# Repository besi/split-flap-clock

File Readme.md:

Split Flap clock or calendar utilising four 28BYJ-48 stepper motors.

## Bill of materials

What is needed for one digit.

| Count | Item                 | Description                       |
|-------|----------------------|-----------------------------------|
| 1     | PCB v2.0             |                                   |
| 1     | Supporting Plate     | Same shape and holes like the PCB |
| 1     | Spacer 2mm           | Spacer for cogwheels              |
| 1     | Hall sensor AH1815-W7| For the unpopulated PCBs only     |
| 1     | 10k Resistor 0306    | For the unpopulated PCBS          |
| 1     | Spool                | 3-D Print with M3 heat insert     |
| 1     | Spool lid            | 3-D Print                         |
| 1     | Cog Stepper          | 3-D Print / Laser cut             |
| 1     | Cog M3               | 3-D Print / Laser cut             |
| 1     | Cog M3 Nut           | 3-D Print / Laser cut             |
| 1     | Magnet 2x1mm         | For spool                         |
| 1     | Motor 28BYJ-48       | 5V Version                        |
| 1     | Motor gasket         | Laser cut                         |
| 12    | Flaps                | Laser cut Flaps                   |
| 1     | 3 Pos JST 2mm Socket | Hall sensor Connection            |
| 1     | 3 Pos JST 2mm Cable  | Hall sensor Connection            |
| 4     | M3 Nuts              | 2 Cogs, 2 Motor                   |
| 5     | M3x8mm Bolt          | 2 Cogs,2 Motor, Spindle,          |
| 3     | M3x5mm Bolt          | 3 Spindle                         |
| 4     | M3 Standoffs 50mm    | Male-Female 6mm thread            |
| 4     | M2.5 Screws          | For Standoffs                     |
| 1     | Washer 5mm 1mm thick | For Driver cogwheel               |
| 2     | Washer 3mm 1mm thick | For cogwheels                     |
| 1     | Zip tie for motor    |                                   |

## Pinout

Motors: 

| Pins        | 1  | 2  | 3  | 4  | Hall  |
|-------------|----|----|----|----|-------|
| **Motor A** | 10 | 9  | 3  | 8  | 18 (7)|
| **Motor B** | 13 | 14 | 21 | 11 | 12    |
| **Motor C** | 40 | 39 | 38 | 6  | 47    |
| **Motor D** | 1  | 2  | 42 | 41 | 48    |

Other GPIOs

| Function       | Pin |
|----------------|-----|
| DCF-77         | 4   |
| SDA / Switch B | 16  |
| SCL / Switch A | 17  |
| Mode           | 0   |
| Neopixel       | 15  |
| Temperature    | 5   |

## Assembly

One assembled PCB which functions as the main board can drive four split flap digits including itself as well as three additional passive digits. Looking from the front of the clock / calendar the unit with the populated PCB is to the very left with the barrel jack protruding outward to the left side.

- On the three unpopulated PCBs the Hall sensors circuitry above the spool axis has to be provided. For this R7 can be shortened using a solder bridge, the Hall sensor (AH1815-W7) as well as the R1 resistor (10k 0603) need to be mounted. C1 (100nF 0603) can be omitted:  

- Using M3x5 screws mount all four motors directly to the corresponding PCB using the spacer where it says "28BYJ-48". The nuts go to the other side of the PCB where the spacer has two cutouts for both nuts.

- On the main board connect the motor to the "Motor A" connector. The cable can be looped and secured using a zip tie threaded through the two holes next to the motor.

- On the main board solder the three switches and the RGB LED to the backside of the PCB.

- Solder the DCF77 connector to the pcb and temporarily tape the ferrite antenna to the PCB to protect the thin copper wires from the coil around the antenna.

- Add cog wheels with the M3x8 screws on two different sides
- Add the spacer
- Add the cover
- Connect all hall sensors
- Prepare the spool 
- Add standoffs female-female or standoffs male-female respectively

- The driving cog wheel is assembled as follows:

        M3x16 + 5 washers + m3-nut-cog + 3 washers

## The PCB

[PCBWay][pcbway] kindly offered to sponsor the manufacturing and assembly of the second iteration of this pcb.

[][pcbway]

In this project the PCBs are used in both the electrical as well as the mechanical realm. The motors and cog wheels are directly mounted onto the pcb and for one clock or calendar four pcbs are stacked together.

The PCBs turned out flawlessly and the ordering process was smooth and efficient.

[pcbway]: https://pcbway.com/g/2jc702

### PCB V2.0

### PCB V1.0

## Flashing the PCB

    cd ~/Downloads
    IMAGE=ESP32_GENERIC_S3-20251209-v1.27.0.bin
    wget https://micropython.org/resources/firmware/$IMAGE -nc
    PORT=/dev/cu.usbmodem14401
    esptool.py --port $PORT erase_flash
    esptool.py --port $PORT --baud 460800 write_flash --flash_size=detect 0 $IMAGE --flash_mode=dout

## Credits

### 3d models
- Credits for the [ESP32 Devkit 3d model](https://grabcad.com/library/esp32-devkitc-v4-1) by [Andrei Golyakov](https://grabcad.com/andrei.golyakov-1)
- Credits for the [SK6814mini 3d model](https://grabcad.com/library/sk6812-mini-sk6814-smd3535-1) by [Laur V](https://grabcad.com/laur.v-1)

### Markdown tables

The Markdown tables were generated using the fabulous tool called [tableconvert](https://tableconvert.com/markdown-generator).

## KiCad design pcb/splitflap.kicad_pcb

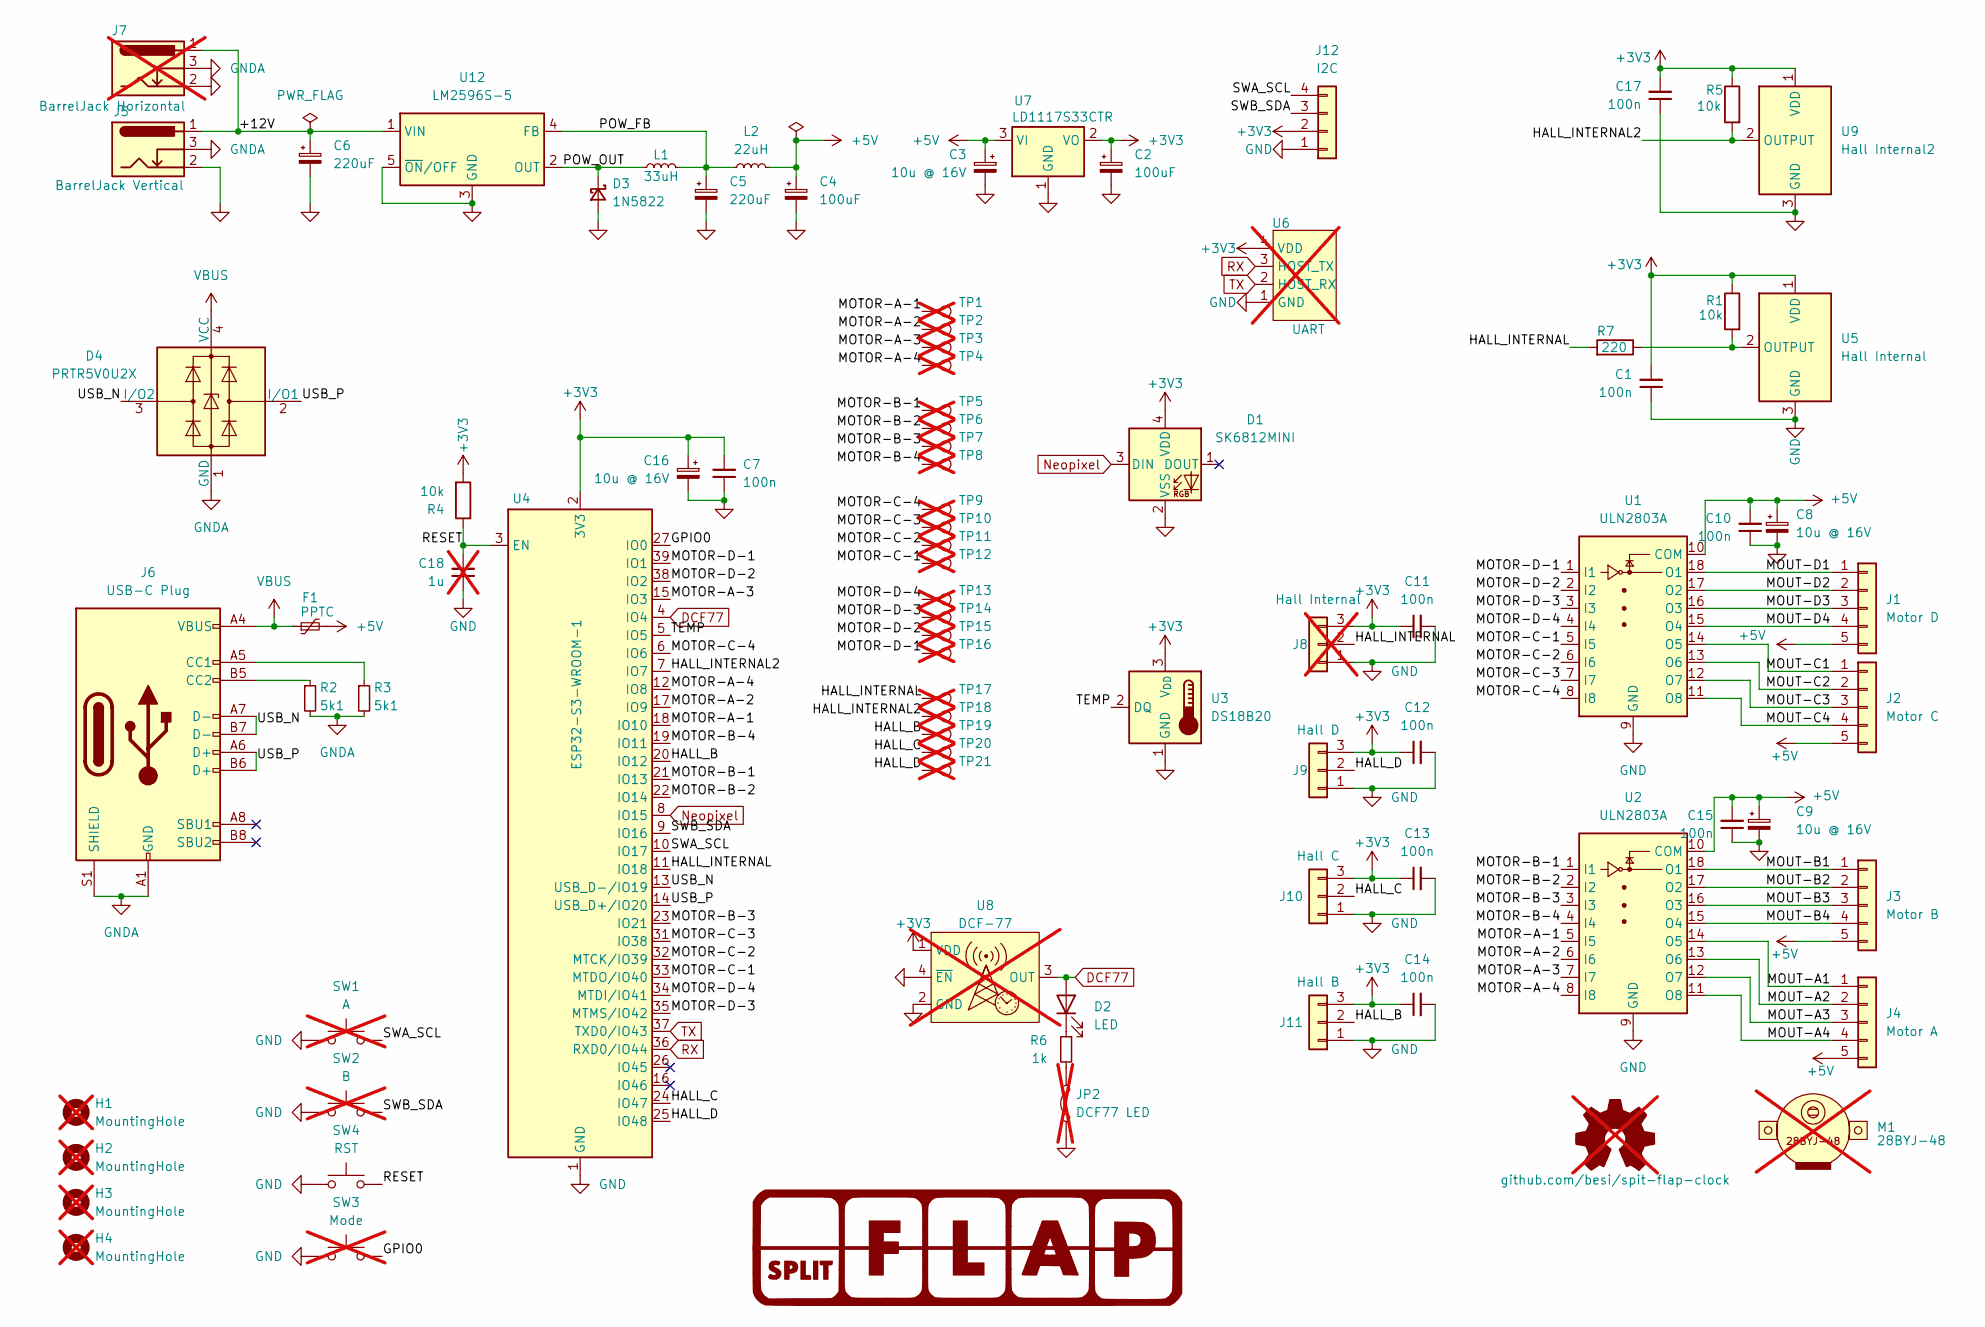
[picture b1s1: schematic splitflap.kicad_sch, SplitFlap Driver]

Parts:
C1, C7, C10, C11, C12, C13, C14, C15, C17: 100n; C_0603_1608Metric; MPN CL10E104KC8VPNC
C2, C4: 100uF; CP_Elec_5x5.3; MPN APXG160ARA101ME61G
C3, C8, C9, C16: 10u @ 16V; CP_Elec_4x5.7; MPN 865080340001
C5, C6: 220uF; CP_Elec_8x11.9; MPN A768KS227M1VLAE024
C18: 1u; C_0805_2012Metric_Pad1.18x1.45mm_HandSolder; MPN CL21B105KOFNNNG; not fitted
D1: SK6812MINI; LED_SK6812MINI_PLCC4_3.5x3.5mm_P1.75mm; MPN 1528-1541-ND
D2: LED; LED_0603_1608Metric_Pad1.05x0.95mm_HandSolder; MPN 150060RS75000
D3: 1N5822; D_DO-201_P15.24mm_Horizontal; MPN 1N5822
D4: PRTR5V0U2X; SOT-143; MPN PRTR5V0U2X,215
F1: PPTC; Fuse_1206_3216Metric; MPN MF-NSMF110/16X-2
H1, H2, H3, H4: MountingHole; MountingHole_3.2mm_M3; MPN X; LCSC DNP; not fitted
J1: Motor D; JST_XH_B5B-XH-A_1x05_P2.50mm_Vertical; MPN B5B-XH-A
J2: Motor C; JST_XH_B5B-XH-A_1x05_P2.50mm_Vertical; MPN B5B-XH-A
J3: Motor B; JST_XH_B5B-XH-A_1x05_P2.50mm_Vertical; MPN B5B-XH-A
J4: Motor A; JST_XH_B5B-XH-A_1x05_P2.50mm_Vertical; MPN B5B-XH-A
J5: BarrelJack Vertical; pj-060a; MPN CP-060A-ND
J6: USB-C Plug; USB_C_Receptacle_GCT_USB4105-xx-A_16P_TopMnt_Horizontal; MPN USB4105-GF-A
J7: BarrelJack Horizontal; BarrelJack_GCT_DCJ200-10-A_Horizontal; MPN 2073-DCJ200-10-A-K1-K-ND; not fitted
J8: Hall Internal; JST_PH_B3B-PH-K_1x03_P2.00mm_Vertical; MPN B3B-PH-K-S; not fitted
J9: Hall D; JST_PH_B3B-PH-K_1x03_P2.00mm_Vertical; MPN B3B-PH-K-S
J10: Hall C; JST_PH_B3B-PH-K_1x03_P2.00mm_Vertical; MPN B3B-PH-K-S
J11: Hall B; JST_PH_B3B-PH-K_1x03_P2.00mm_Vertical; MPN B3B-PH-K-S
J12: I2C; JST_SH_BM04B-SRSS-TB_1x04-1MP_P1.00mm_Vertical; MPN BM04B-SRSS-TB
JP2: DCF77 LED; SolderJumper-2_P1.3mm_Bridged_RoundedPad1.0x1.5mm; MPN X; not fitted
L1: 33uH; L_APV_ANR6028; MPN NR6028T330M
L2: 22uH; L_APV_ANR5045; MPN TYS5040220M-10
M1: 28BYJ-48; 28byj; MPN 28BYJ-48; not fitted
OSHW1: github.com/besi/spit-flap-clock; OSHW-Symbol_6.7x6mm_SilkScreen; MPN X; not fitted
R1, R5: 10k; R_0603_1608Metric; MPN CR0603-FX-1002ELF
R2, R3: 5k1; R_0603_1608Metric; MPN CR0603-FX-5101ELF
R4: 10k; R_0603_1608Metric_Pad0.98x0.95mm_HandSolder; MPN CR0603-FX-1002ELF
R6: 1k; R_0603_1608Metric; MPN CR0603-JW-102ELF
R7: 220; R_0603_1608Metric; MPN CR0603-JW-221ELF
SW1: A; SW_Push_1P1T_NO_Vertical_Wuerth_434133025816; MPN PTS815SJM250SMTRLFS; not fitted
SW2: B; SW_Push_1P1T_NO_Vertical_Wuerth_434133025816; MPN PTS815SJM250SMTRLFS; not fitted
SW3: Mode; SW_Push_1P1T_NO_Vertical_Wuerth_434133025816; MPN PTS815SJM250SMTRLFS; not fitted
SW4: RST; SW_Push_1P1T_NO_Vertical_Wuerth_434133025816; MPN PTS815SJM250SMTRLFS
TP1, TP2, TP3, TP4, TP5, TP6, TP7, TP8, TP9, TP10, TP11, TP12, TP13, TP14, TP15, TP16, TP17, TP18, TP19, TP20, TP21: TestPoint; TestPoint_Pad_D1.0mm; MPN X; not fitted
U1, U2: ULN2803A; SOP-18_7.495x11.515mm_P1.27mm; MPN 4518-ULN2803ATR-ND
U3: DS18B20; TO-92S; MPN 4518-DS18B20-ND
U4: ESP32-S3-WROOM-1; MPN ESP32-S3-WROOM-1-N4
U5: Hall Internal; SC-59_Handsoldering; MPN AH1815-W-7
U6: UART; PinHeader_1x04_P2.54mm_Vertical; MPN X; not fitted
U7: LD1117S33CTR; SOT-223-3_TabPin2; MPN LD1117S33CTR
U8: DCF-77; dcf77; MPN X; not fitted
U9: Hall Internal2; SC-59_Handsoldering; MPN AH1815-W-7
U12: LM2596S-5; TO-263-5_TabPin3; MPN 5399-LM2596S-5.0CT-ND

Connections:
+3V3: C1.2, C2.1, C7.2, C11.1, C12.1, C13.1, C14.1, C16.1, C17.2, D1.4 (VDD), J8.3, J9.3, J10.3, J11.3, J12.2, R1.1, R4.2, R5.1, U3.3 (V_{DD}), U4.2 (3V3), U5.1 (VDD), U6.4 (VDD), U7.2 (VO), U8.1 (VDD), U9.1 (VDD)
+5V: C3.1, C4.1, C8.1, C9.1, C10.2, C15.2, F1.2, J1.5, J2.5, J3.5, J4.5, L2.2, U1.10 (COM), U2.10 (COM), U7.3 (VI)
/+12V: C6.1, J5.1, J7.1, U12.1 (VIN)
/GPIO0: SW3.2, U4.27 (IO0)
/HALL_B: J11.2, TP19.1, U4.20 (IO12)
/HALL_C: J10.2, TP20.1, U4.24 (IO47)
/HALL_D: J9.2, TP21.1, U4.25 (IO48)
/HALL_INTERNAL: J8.2, R7.2, TP17.1, U4.11 (IO18)
/HALL_INTERNAL2: R5.2, TP18.1, U4.7 (IO7), U9.2 (OUTPUT)
/MOTOR-A-1: TP1.1, U2.5 (I5), U4.18 (IO10)
/MOTOR-A-2: TP2.1, U2.6 (I6), U4.17 (IO9)
/MOTOR-A-3: TP3.1, U2.7 (I7), U4.15 (IO3)
/MOTOR-A-4: TP4.1, U2.8 (I8), U4.12 (IO8)
/MOTOR-B-1: TP5.1, U2.1 (I1), U4.21 (IO13)
/MOTOR-B-2: TP6.1, U2.2 (I2), U4.22 (IO14)
/MOTOR-B-3: TP7.1, U2.3 (I3), U4.23 (IO21)
/MOTOR-B-4: TP8.1, U2.4 (I4), U4.19 (IO11)
/MOTOR-C-1: TP12.1, U1.5 (I5), U4.33 (MTDO/IO40)
/MOTOR-C-2: TP11.1, U1.6 (I6), U4.32 (MTCK/IO39)
/MOTOR-C-3: TP10.1, U1.7 (I7), U4.31 (IO38)
/MOTOR-C-4: TP9.1, U1.8 (I8), U4.6 (IO6)
/MOTOR-D-1: TP16.1, U1.1 (I1), U4.39 (IO1)
/MOTOR-D-2: TP15.1, U1.2 (I2), U4.38 (IO2)
/MOTOR-D-3: TP14.1, U1.3 (I3), U4.35 (MTMS/IO42)
/MOTOR-D-4: TP13.1, U1.4 (I4), U4.34 (MTDI/IO41)
/MOUT-A1: J4.1, U2.14 (O5)
/MOUT-A2: J4.2, U2.13 (O6)
/MOUT-A3: J4.3, U2.12 (O7)
/MOUT-A4: J4.4, U2.11 (O8)
/MOUT-B1: J3.1, U2.18 (O1)
/MOUT-B2: J3.2, U2.17 (O2)
/MOUT-B3: J3.3, U2.16 (O3)
/MOUT-B4: J3.4, U2.15 (O4)
/MOUT-C1: J2.1, U1.14 (O5)
/MOUT-C2: J2.2, U1.13 (O6)
/MOUT-C3: J2.3, U1.12 (O7)
/MOUT-C4: J2.4, U1.11 (O8)
/MOUT-D1: J1.1, U1.18 (O1)
/MOUT-D2: J1.2, U1.17 (O2)
/MOUT-D3: J1.3, U1.16 (O3)
/MOUT-D4: J1.4, U1.15 (O4)
/POW_FB: C5.1, L1.2, L2.1, U12.4 (FB)
/POW_OUT: D3.1 (K), L1.1, U12.2 (OUT)
/RESET: C18.2, R4.1, SW4.2, U4.3 (EN)
/SWA_SCL: J12.4, SW1.2, U4.10 (IO17)
/SWB_SDA: J12.3, SW2.2, U4.9 (IO16)
/TEMP: U3.2 (DQ), U4.5 (IO5)
/USB_N: D4.3 (I/O2), J6.A7 (D-), J6.B7 (D-), U4.13 (USB_D-/IO19)
/USB_P: D4.2 (I/O1), J6.A6 (D+), J6.B6 (D+), U4.14 (USB_D+/IO20)
DCF77: D2.2 (A), U4.4 (IO4), U8.3 (OUT)
GND: C1.1, C2.2, C3.2, C4.2, C5.2, C6.2, C7.1, C8.2, C9.2, C10.1, C11.2, C12.2, C13.2, C14.2, C15.1, C16.2, C17.1, C18.1, D1.2 (VSS), D3.2 (A), J5.2, J7.2, J8.1, J9.1, J10.1, J11.1, J12.1, JP2.1 (A), SW1.1, SW2.1, SW3.1, SW4.1, U1.9 (GND), U2.9 (GND), U3.1 (GND), U4.1 (GND), U4.40 (GND), U4.41 (GND), U5.3 (GND), U6.1 (GND), U7.1 (GND), U8.2 (GND), U8.4 (~EN), U9.3 (GND), U12.3 (GND), U12.5 (~ON/OFF)
GNDA: D4.1 (GND), J5.3, J6.A1 (GND), J6.A12 (GND), J6.B1 (GND), J6.B12 (GND), J6.S1 (SHIELD), J7.3, R2.2, R3.2
Neopixel: D1.3 (DIN), U4.8 (IO15)
unnamed: D2.1 (K), R6.1
unnamed: J6.A5 (CC1), R3.1
unnamed: J6.B5 (CC2), R2.1
unnamed: JP2.2 (B), R6.2
unnamed: R1.2, R7.1, U5.2 (OUTPUT)
RX: U4.36 (RXD0/IO44), U6.3 (HOST_TX)
TX: U4.37 (TXD0/IO43), U6.2 (HOST_RX)
VBUS: D4.4 (VCC), F1.1, J6.A4 (VBUS), J6.A9 (VBUS), J6.B4 (VBUS), J6.B9 (VBUS)

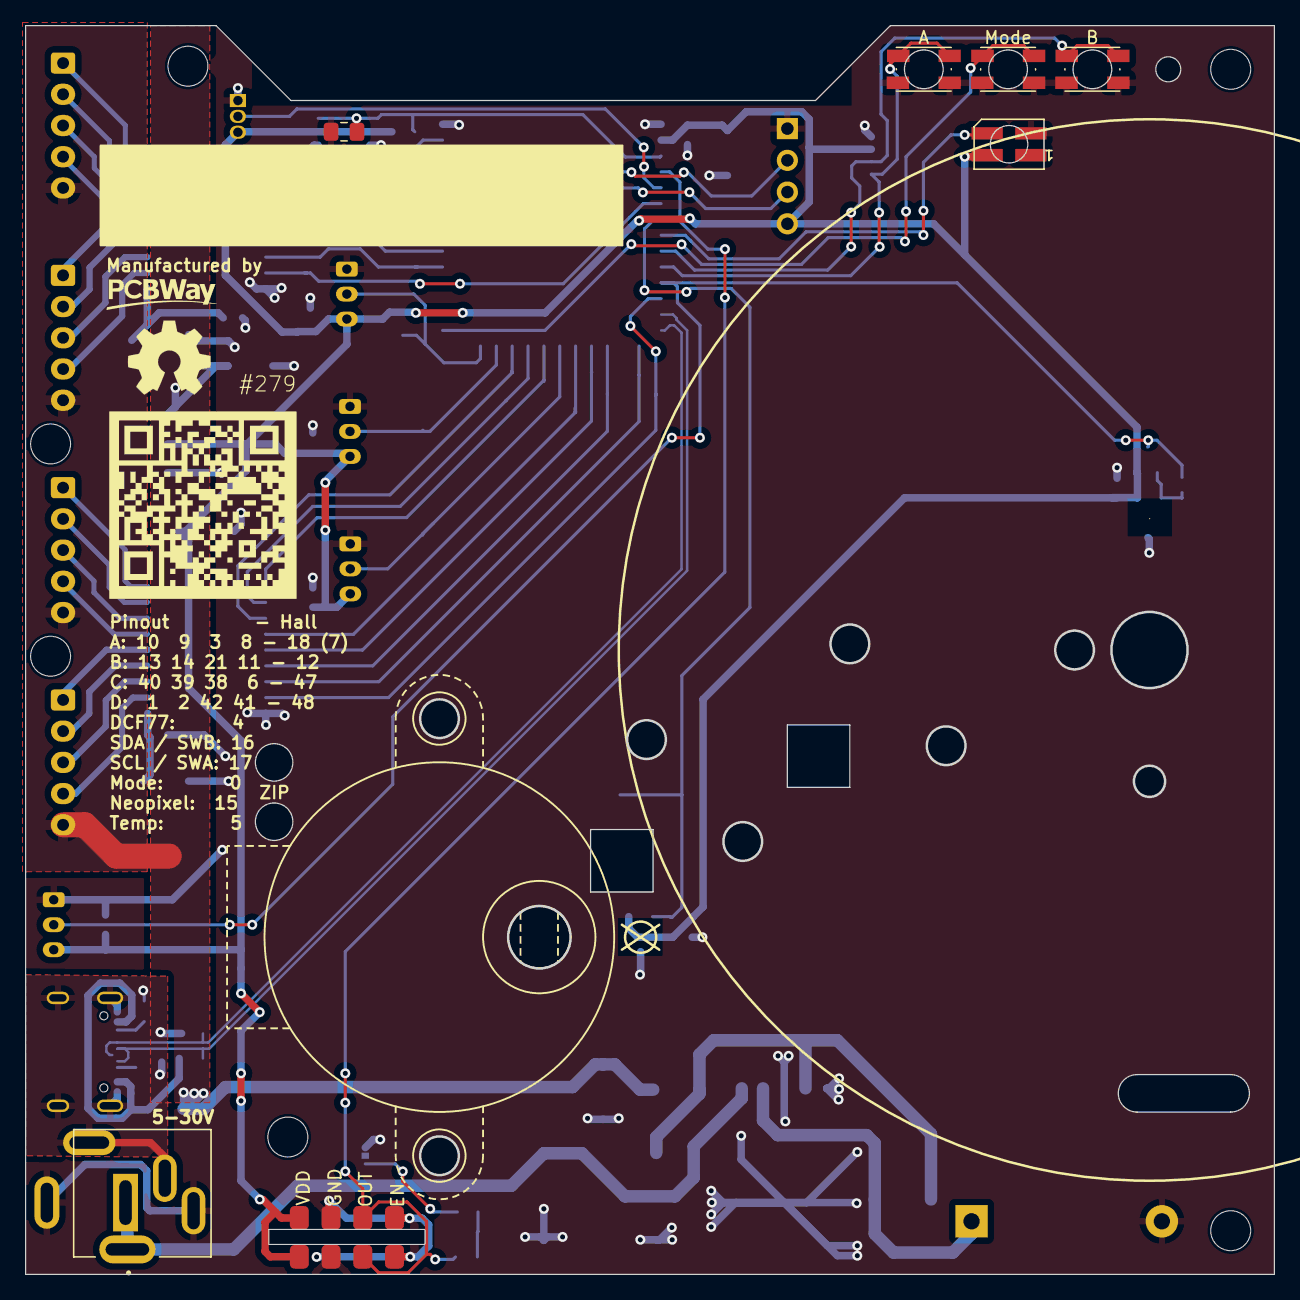
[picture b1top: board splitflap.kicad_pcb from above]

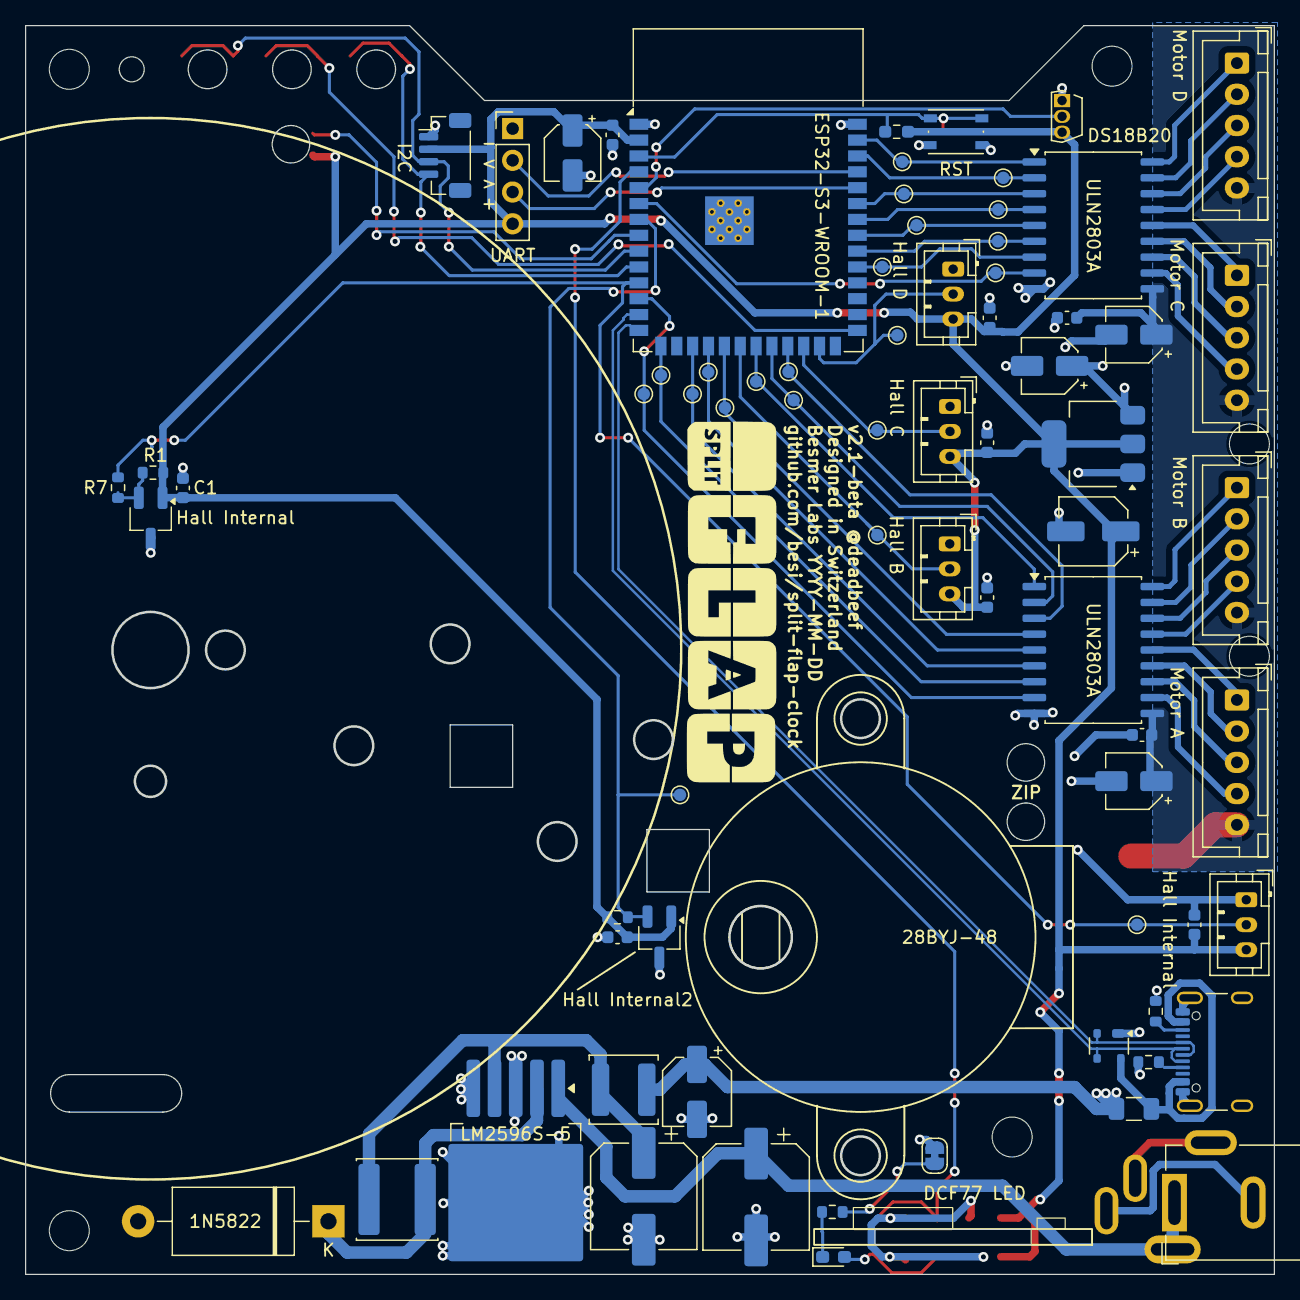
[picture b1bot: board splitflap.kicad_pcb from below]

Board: 2 copper layers, 99.9 x 99.9 mm, 88 parts (81 on the bottom side), 61 nets.

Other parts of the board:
H5, H6: MountingHole; MountingHole_3.2mm_M3

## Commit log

2025-01-18 Add readme
2025-01-19 Add dxf for the case - v1
2025-01-19 Don't add the makercase screenshot
2025-01-19 Added 2mm housing
2025-01-19 Fixed wrong material thickness
2025-01-19 Updated screenshot
2025-01-20 Add software
2025-01-20 Add flaps of v2
2025-01-21 Add 3d files
2025-01-21 new case for v2
2025-01-21 Add filet to front
2025-01-21 Add stl
2025-01-21 update screenshot
2025-01-25 Add intial pcb for the split flap calender multi-motor setup
2025-01-26 Silkscreen and documentation
2025-01-26 Add Logo
2025-01-26 Silkscreen and hall sensor breakout cleanup
2025-01-26 Panelise the Hall sensor breakout
2025-01-26 Add a barrel jack and include all hall breakouts in the schematic
2025-01-26 Add measurements
2025-01-26 Cleanup schematic
2025-01-26 Add four buttons A, B, GPIO0 and RST
2025-01-26 Set the board origin for step export and prepare for next release
2025-01-28 Add esp 32 wroom step file
2025-01-29 Make sure mouse bites aren't deleted upon import
2025-02-03 Add 12V-enabled power supply
2025-02-04 Add missing footprint
2025-02-04 Add qwiic adapter
2025-02-04 Run DRC and ERC
2025-02-04 .gitignore
2025-02-04 Prepare for production
2025-02-05 Version 1.1-beta
2025-02-05 Upcoming release
2025-02-08 Add gears
2025-02-09 Allow skipping the WIFI in boot.py
2025-02-09 Add 18n gears
2025-02-17 Make SOIC16 package of ULN2003 more wide and label both inductors with silkscreen
2025-02-17 Add package to schematic for SOIC16 ULN2003
2025-02-18 Hardware test
    See #1
2025-02-18 Test for buttons
    see #1
2025-02-22 Add 3d model of the pcb
2025-02-28 Update to stepper code
2025-02-28 Alternate aparently more responsive motor mapping
2025-02-28 Allow testing all the steppers
2025-02-28 Add micropython board identifier
2025-02-28 Add upcoming todo
2025-03-01 Add todos
2025-03-01 HW Test script so the programming in main.py can start
2025-03-01 Add digit class which allows to control one digit
2025-03-01 fine tune the calibration process for the digits
2025-03-01 Allow to jump to a given value
2025-03-02 Update schematic to aid troubleshooting
2025-03-04 Update digit to show all four digits
2025-03-04 Enable Wifi
2025-03-04 show the time at startup
2025-03-04 cleanup code
2025-03-04 Fix wrong labels in PCB
2025-03-04 Fix an error with a reference to the wrong hall sensor
2025-03-04 Adjust for angle
2025-03-04 Rework 1
    Per EE.SO answer https://electronics.stackexchange.com/a/740530/10810
2025-03-04 Rework 3
    Now the signal flow is the recommended way: inputs far away from power outputs. The Hall sensor connectors have been moved to the front of the PCB.
2025-03-04 Rework 2
    To be conservative, the traces driving the ULN2003s have been separated out, to prevent capacitive coupling between them. It's "cargo cult engineering", but since we can do it without trouble, how ab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
2025-03-04 Rework 4
    The trace from the 12V input capacitor to the switcher ran on the bottom layer, making for a rather deep cut in the ground plane. This trace has been partially moved to the top layer, avoiding the cu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
2025-03-04 Rework 5
    The schematic was separated into two sheets, and made easier to follow.
    The Neopixels were connected in parallel. They should be in series.
    The I2C mezzanine board was centered relative to the ESP module.
2025-03-05 Rework 6
    Added power flags to external power inputs. Fixed Motor connector pins from Unspecified to Passive, per KiCad fashion. Made the ERC pass without exclusions.
    Added power decoupling to Hall sensor connectors and to the Neopixels.
    Moved the IN test point for better probing accessibility. Test points use teardrop connections for integrity in face of probing.
    Added a ground clip area for scope probes etc.
    Added a 3D model of the pushbuttons.
    Rework 6
2025-03-05 Ignore library backup files (.bak).
2025-03-05 Add an image of the working prototype
2025-03-08 Draft of v2 board to be imported in Fusion360
2025-03-11 SW: Add the corrections as a seperate variable
2025-03-11 Allow to skip the offset move after the calibration in order to save revolutions at startup
2025-03-11 Cleanup calibration and main.py
2025-03-14 V2 WIP
2025-03-14 Add step files of the libraries
2025-03-14 Make the zip tie holes vertical
2025-03-14 Make cable winding holes bigger
2025-03-15 Small changes
    - Rename 4341x30258x6_rev1.stp to 434133025816.step
2025-03-15 Cleanup libraries
2025-03-15 Add extra test point for IO7 and an additional hall sensor for Hall A
2025-03-16 Make GNDA a power line
2025-03-16 Cleanup tracks
2025-03-17 Silkscreen improvements
2025-03-18 Show the current day after calibration of each digit
2025-03-18 Added 3d model of the SK6812 mini
2025-03-20 Add optional LED for DCF receiver
2025-03-20 Add two Hall sensors to the current board so that the amount of backlash can be registered
2025-03-20 Remapping the motors ABCD to match the connectors on the board
2025-03-20 Add capacitors for hall sensors power pins
2025-03-20 DNP components and bigger pads for hand solder items
2025-03-20 Run DRC
2025-03-21 Add new pcb design to the Readme
2025-03-21 Add flap stop slot
2025-03-21 Add a PPTC fuse to the USB connection
2025-03-21 Add test points for motor input signals and hall sensors
2025-03-21 Use 0603 for resistors and capacitors
2025-03-21 Update DNP field
2025-03-22 Add ESD protection for the USB-C socket
2025-03-22 Change package of the temperature sensor
2025-03-23 Cleanup MPNs
2025-03-23 Finalise MPNs
2025-03-23 Finalise the part’s MPN
2025-03-23 Unambiguous MPN for the TVS diode array
2025-03-23 Move silkscreen to Fab layers
2025-03-24 Populate the barrel jack on the back (if possible) and add a keep out zone for both hall sensors just in case
2025-03-24 Add logo to the PCB
2025-03-24 Silkscreen: Logo / Date / Commit Placeholder / Labels / PCB Way logo
2025-03-24 Add Pinout
2025-03-25 Fix HALL_INTERNAL label
    The layout is not affected
2025-03-25 Move images to `assets` folder
2025-03-25 Add version 1 and 2 to the Readme
2025-03-25 Add PCBWay sponsoring note to Readme
2025-03-25 Cleanup schematics
2025-03-25 Move vias out of the pads
2025-03-25 Correlate footprints according to the feedback from the Fab-house
2025-03-25 Add step model for the NR6028T330M inductor
2025-03-25 Prepare for fab-house
2025-03-25 Update credits in Readme
2025-03-26 Add Pinout to the Reamde
2025-03-26 Prepare for next release
2025-03-26 Line breaks in readme
2025-04-10 Add 18-theethed gears
2025-04-10 Add v1.2 stl files
2025-04-10 Add stl files based on fusion v19
2025-04-10 Cleanup stl files
2025-04-10 Add pcb for making support plates
2025-04-10 Add flaps SVG
2025-04-10 Add plot directory
2025-04-10 Settings for plotting
2025-05-04 Add credits for the markdown tables
2025-05-04 Add bill of materials for the V2.0 PCB
2025-05-07 Add spacer
2025-05-07 Add cog wheels as stl epxports
2025-05-07 Add washers to BOM
2025-05-07 Update v2 3d printing parts
2025-05-07 Add spacers
2025-05-07 Make some room inside the spacer
2025-05-07 Add zip ties to BOM
2025-05-08 m3 holes are now 3.2 mm and the cogs are 2.8mm thick
2025-05-08 Reference heat insert for 3d printed spool
2025-05-08 Update Backplate spacer
2025-05-08 Update spool and spool lid
2025-05-09 Add preliminary Flap design
2025-05-10 Describe how the spool cog is assembled
2025-05-10 Describe which hall sensor is used
2025-05-10 Configure first stepper for v2 pcb
2025-05-10 Fix utime vs. time lib
2025-05-10 make the cogs 2.5 mm and improve the magnet holder to better fit the 2mm magnets
2025-05-10 Add lower part to the flap
2025-05-16 Assembly notes
2025-05-16 Update the Readme with details on how to flash the device
2025-05-16 Fix error with utime
2025-05-16 Enable all digits
2025-05-16 Configure for v2.0 pcb
2025-05-18 Change TX Power to 5 rather than 20
    fixes #10
2025-05-18 Test the neopixel
    See #7
2025-05-18 Show the entire date upon update
2025-05-18 Show blank number for single digits
2025-05-18 Test Neopixel
    See #7
2025-05-18 Test buttons and I2C
    See #7
2025-05-18 The number digits should both start at 0
2025-05-24 Update digit position
2025-05-24 Formatting
2025-05-24 Only activate the wifi interface if internet is enabled
2025-05-25 Add flap toucher dxf
2025-05-25 Add dependencies
2025-05-26 Add flap pair
2025-05-26 Ignore lightburn files
2025-05-27 Add photo of the finished calendar
2025-05-27 Typo
2025-05-27 Flap changes: 7mm Tab / Extra wiggle 0.5 each side / round of Flap corners
2025-06-01 Show an empty flap for leading zeros of the date
2025-06-08 Make the 11th flap the blank so that a new number is more quickly shown
2025-06-08 Update the neopixel pin
2025-06-08 Show Blank Flaps upon calibration
    This allows a better demo effect since the date is not given away right away
2025-06-08 Update Neopixel Pin for v2 pcb
2025-06-14 Add floating calibration when passing the hall sensor during operation
    Fixes #5
2025-06-15 Cleanup digit code
2025-06-15 Show the month upon calibration
2025-06-15 Display negative corrections
2025-06-15 Apply the calculated correction when executing the next move
    Fixes #5
2025-06-15 Round the positions
2025-06-19 Denote R1 and R7 since they need to be populated on some PCBs after the fact
    See #14
2025-06-19 Add zip tie label
    See #14
2025-06-20 Add initial assembly section to the Readme
    See #14
2025-07-02 Fix neopixel pin
2025-07-02 Allow to show both the time or the date
2025-07-03 Update the assembly
2025-07-16 Extend the PCB section of the Readme.md
2025-08-22 Calibrated offsets of the clock digits
2025-08-22 Show a startup pattern
2025-08-22 Check the time more frequently
2025-08-22 Add screenshot of the clock
2025-08-22 Extend credits section
2025-09-06 Only allow to show digits if they've been calibrated
2025-09-06 Show the time as soon as possible
2025-12-21 Show the time as quickly as possible
2025-12-21 Code formatting
2025-12-21 Micropython 1.27 does no longer require the 4M variant
